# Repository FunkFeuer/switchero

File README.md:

# switchero
I2C controlled power switch with current and fault limiting.

Originally created by [@wnagele](https://github.com/wnagele) and [@oe1rfc](https://github.com/oe1rfc) for switching USB power supplies of embedded boards in the [FunkFeuer Wien Housing](http://housing.funkfeuer.at).

## License
All work is licensed under [CC BY-SA 3.0](LICENSE.txt).

## Schematic and Gerbers
Gerbers of the revisions can be found in the [releases](https://github.com/FunkFeuer/switchero/releases). The schematics, etc. are provided in KiCad project format.

## Bill of Material
The BoM is available as [CSV file](switchero.csv).

## Board
The board is a 4 layer PCB and about 60x60mm.

This is a quick 3D render of the board:

Front and back of an assembled board (pardon the "questionable" soldering work):

Mounted with daisy chained I2C for the housing project:

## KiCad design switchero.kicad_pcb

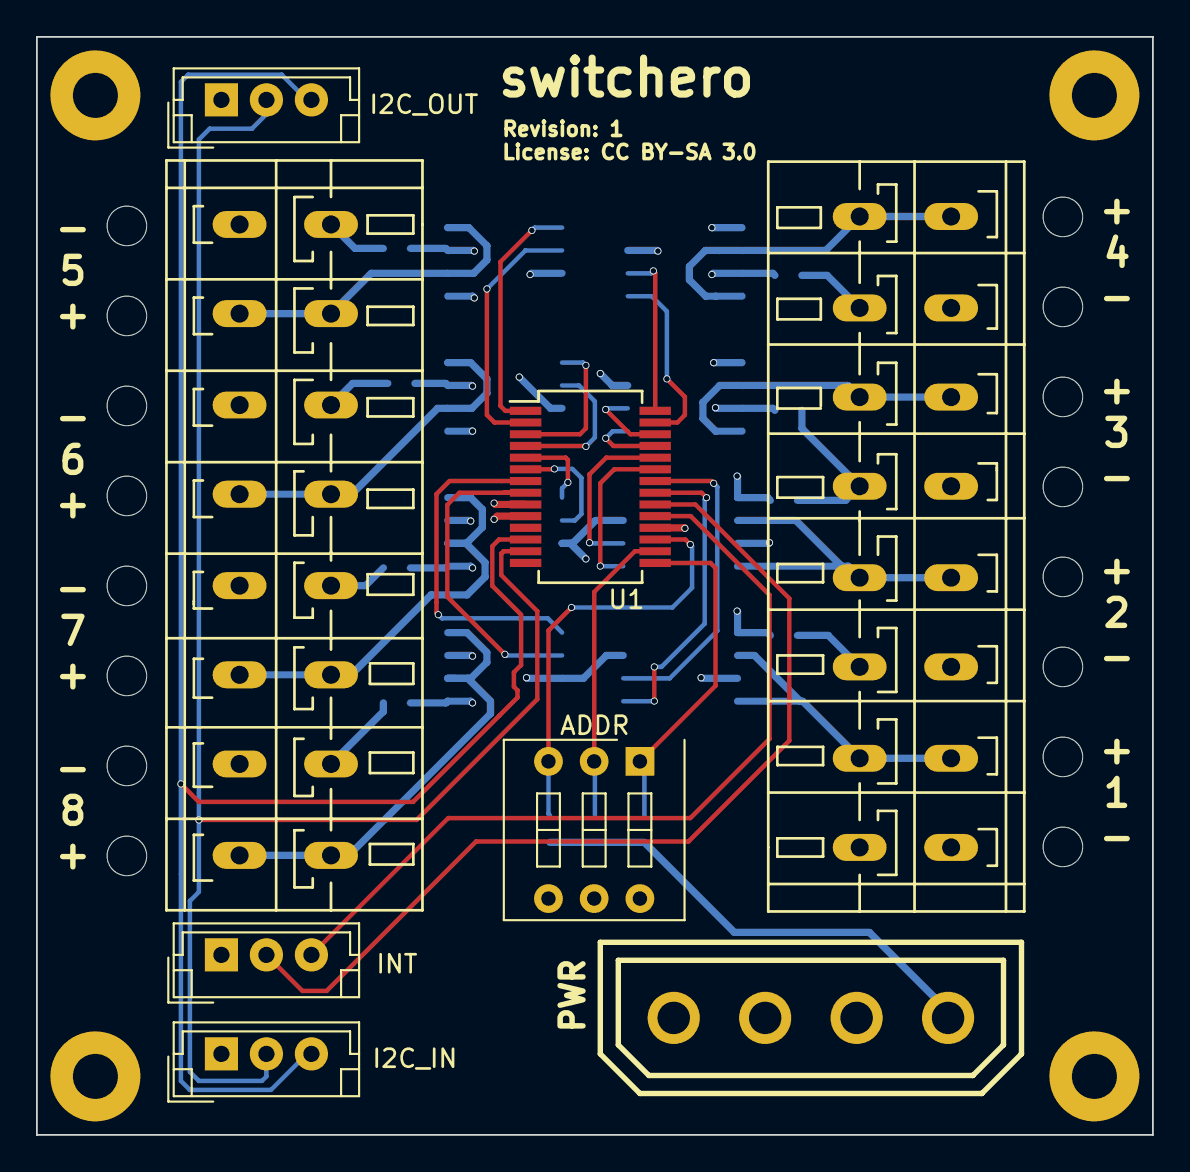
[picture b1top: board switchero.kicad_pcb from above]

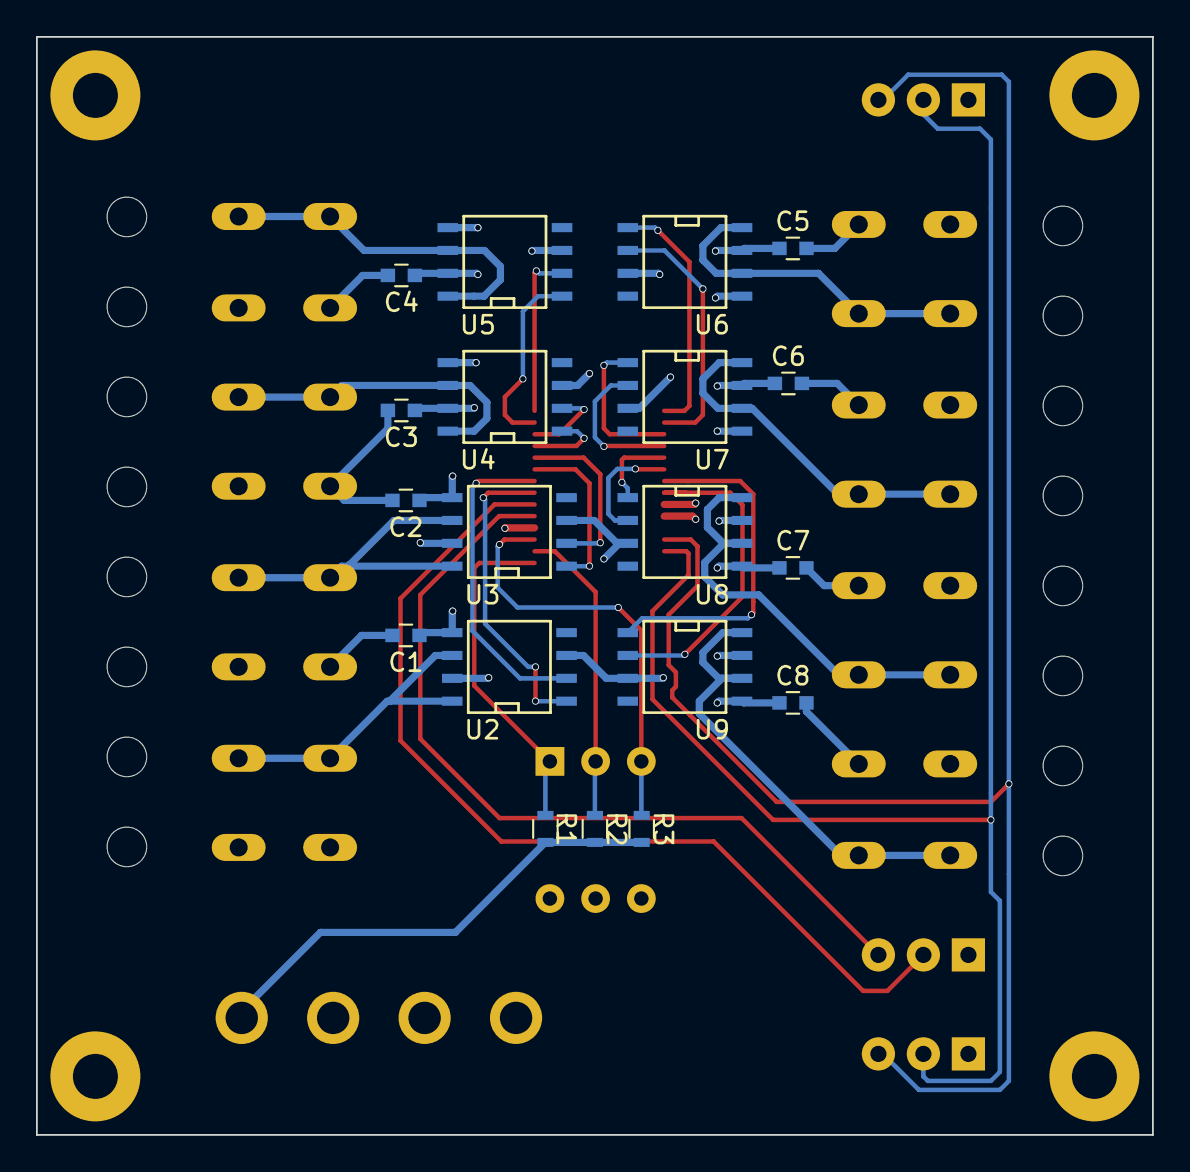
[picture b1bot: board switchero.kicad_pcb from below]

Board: 4 copper layers, 62.0 x 61.0 mm, 27 parts (19 on the bottom side), 33 nets.

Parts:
C1, C2, C3, C4, C5, C6, C7, C8: 0.1u; C_0603
P1: ADDR; SW_DIP_x3_W7.62mm_Slide
P2: I2C_IN; JST_EH_B03B-EH-A_03x2.50mm_Straight
P3: PWR; conn_hdd_15-24-4449
P4: INT; JST_EH_B03B-EH-A_03x2.50mm_Straight
P5: OUT2; TerminalBlock_WAGO-236_2Stift_RM5mm_8pol
P6: OUT1; TerminalBlock_WAGO-236_2Stift_RM5mm_8pol
P7: I2C_OUT; JST_EH_B03B-EH-A_03x2.50mm_Straight
R1, R2, R3: 4.7k; R_0603
U1: MCP23017; SSOP-28_5.3x10.2mm_Pitch0.65mm
U2, U3, U4, U5, U6, U7, U8, U9: MIC2505; SOIC-8-N

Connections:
GND: C1.2, C2.2, C3.2, C4.2, C5.2, C6.2, C7.2, C8.2, P1.4, P1.5, P1.6, P2.1, P3.2, P3.3, P4.1, P5.1, P5.3, P5.5, P5.7, P6.1, P6.3, P6.5, P6.7, P7.1, U1.10, U2.3, U3.3, U4.3, U5.3, U6.3, U7.3, U8.3, U9.3
INTA: P4.2, U1.20
INTB: P4.3, U1.19
unnamed: P1.1, R1.1, U1.15
unnamed: P1.2, R2.1, U1.16
unnamed: P1.3, R3.1, U1.17
unnamed: U1.1, U6.1
unnamed: U1.2, U6.2
unnamed: U1.3, U7.1
unnamed: U1.4, U7.2
unnamed: U1.5, U8.1
unnamed: U1.6, U8.2
unnamed: U1.7, U9.1
unnamed: U1.8, U9.2
unnamed: U1.21, U2.1
unnamed: U1.22, U2.2
unnamed: U1.23, U3.1
unnamed: U1.24, U3.2
unnamed: U1.25, U4.1
unnamed: U1.26, U4.2
unnamed: U1.27, U5.1
unnamed: U1.28, U5.2
PWR: C1.1, C2.1, C3.1, C4.1, C5.1, C6.1, C7.1, C8.1, P3.4, R1.2, R2.2, R3.2, U1.9, U1.18, U2.5, U2.7, U3.5, U3.7, U4.5, U4.7, U5.5, U5.7, U6.5, U6.7, U7.5, U7.7, U8.5, U8.7, U9.5, U9.7
SCK: P2.3, P7.3, U1.12
SDA: P2.2, P7.2, U1.13
SW1: P6.2, U2.6, U2.8
SW2: P6.4, U3.6, U3.8
SW3: P6.6, U4.6, U4.8
SW4: P6.8, U5.6, U5.8
SW5: P5.2, U6.6, U6.8
SW6: P5.4, U7.6, U7.8
SW7: P5.6, U8.6, U8.8
SW8: P5.8, U9.6, U9.8

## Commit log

2017-05-01 :sunrise:
2017-05-01 Add license
2017-05-06 Old reference
2017-05-06 Add BoM
2017-05-06 Add docs
2017-05-28 Some more pics

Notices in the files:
switchero.kicad_pcb:
License: CC BY-SA 3.0
